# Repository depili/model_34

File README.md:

# Files for Model 34 tape and card punch control

The circuit is based on the example in the manual. This repository includes the hardware as a kicad project, the software for the arduino for usb serial communications and a 3d printable drive belt replacement.

The belt was printed in TPU and seems to last well, at least in light use.

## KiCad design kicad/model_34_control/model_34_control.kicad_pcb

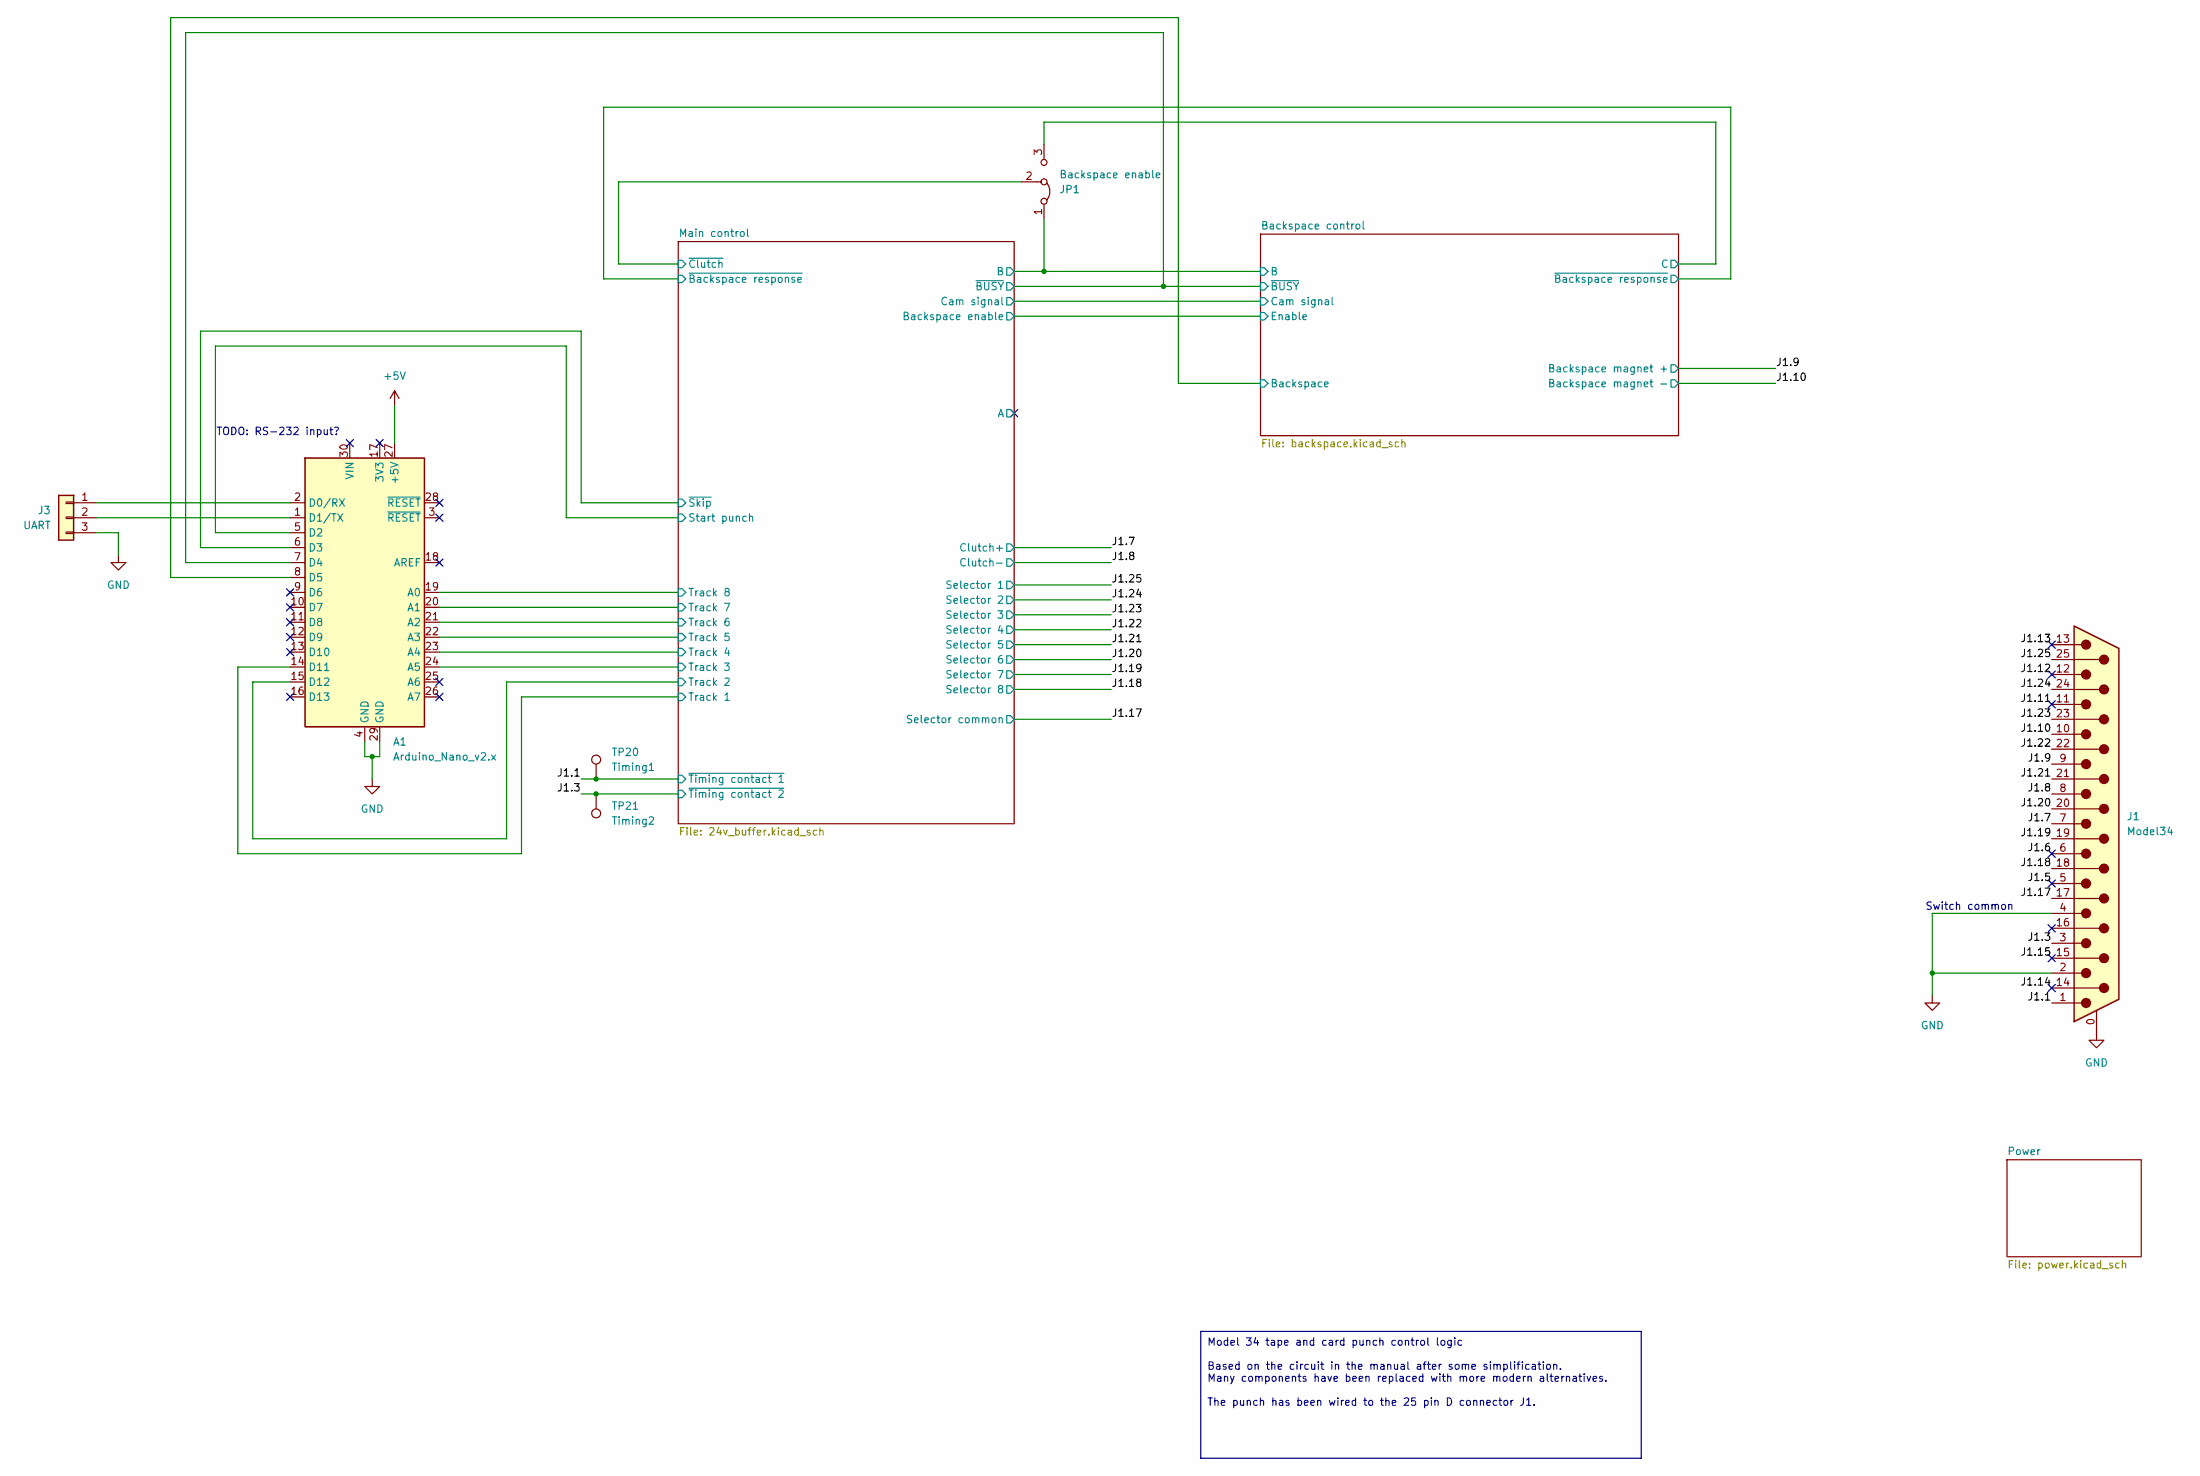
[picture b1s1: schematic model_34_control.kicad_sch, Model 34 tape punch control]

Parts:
A1: Arduino_Nano_v2.x; Arduino_Nano
J1: Model34; DSUB-25_Female_Horizontal_P2.77x2.84mm_EdgePinOffset9.90mm_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
J3: UART; PinHeader_1x03_P2.54mm_Vertical
JP1: Backspace enable; PinHeader_1x03_P2.54mm_Vertical
TP20: Timing1; TestPoint_Loop_D2.54mm_Drill1.5mm_Beaded
TP21: Timing2; TestPoint_Loop_D2.54mm_Drill1.5mm_Beaded

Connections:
+5V: A1.27 (+5V); also elsewhere on the board
+24V: J1.7, J1.9, J1.17; also elsewhere on the board
/Backspace control/B: JP1.1 (A); also elsewhere on the board
/Backspace control/Backspace: A1.8 (D5); also elsewhere on the board
/Backspace control/C: JP1.3 (B); also elsewhere on the board
/Backspace control/~BUSY: A1.7 (D4); also elsewhere on the board
/J1.1: J1.1, TP20.1; also elsewhere on the board
/J1.3: J1.3, TP21.1; also elsewhere on the board
/J1.5: J1.5
/J1.6: J1.6
/J1.8: J1.8; also elsewhere on the board
/J1.10: J1.10; also elsewhere on the board
/J1.11: J1.11
/J1.12: J1.12
/J1.13: J1.13
/J1.14: J1.14
/J1.15: J1.15
/J1.18: J1.18; also elsewhere on the board
/J1.19: J1.19; also elsewhere on the board
/J1.20: J1.20; also elsewhere on the board
/J1.21: J1.21; also elsewhere on the board
/J1.22: J1.22; also elsewhere on the board
/J1.23: J1.23; also elsewhere on the board
/J1.24: J1.24; also elsewhere on the board
/J1.25: J1.25; also elsewhere on the board
/Main control/Start punch: A1.5 (D2); also elsewhere on the board
/Main control/Track 1: A1.14 (D11); also elsewhere on the board
/Main control/Track 2: A1.15 (D12); also elsewhere on the board
/Main control/Track 3: A1.24 (A5); also elsewhere on the board
/Main control/Track 4: A1.23 (A4); also elsewhere on the board
/Main control/Track 5: A1.22 (A3); also elsewhere on the board
/Main control/Track 6: A1.21 (A2); also elsewhere on the board
/Main control/Track 7: A1.20 (A1); also elsewhere on the board
/Main control/Track 8: A1.19 (A0); also elsewhere on the board
/Main control/~Clutch: JP1.2 (C); also elsewhere on the board
/Main control/~Skip: A1.6 (D3); also elsewhere on the board
GND: A1.4 (GND), A1.29 (GND), J1.0 (PAD), J1.2, J1.4, J3.3; also elsewhere on the board
unnamed: A1.2 (D0/RX), J3.1
unnamed: A1.1 (D1/TX), J3.2

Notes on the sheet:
Model 34 tape and card punch control logic Based on the circuit in the manual after some simplification. Many components have been replaced with more modern alternatives. The punch has been wired to the 25 pin D connector J1.
TODO: RS-232 input?
Switch common

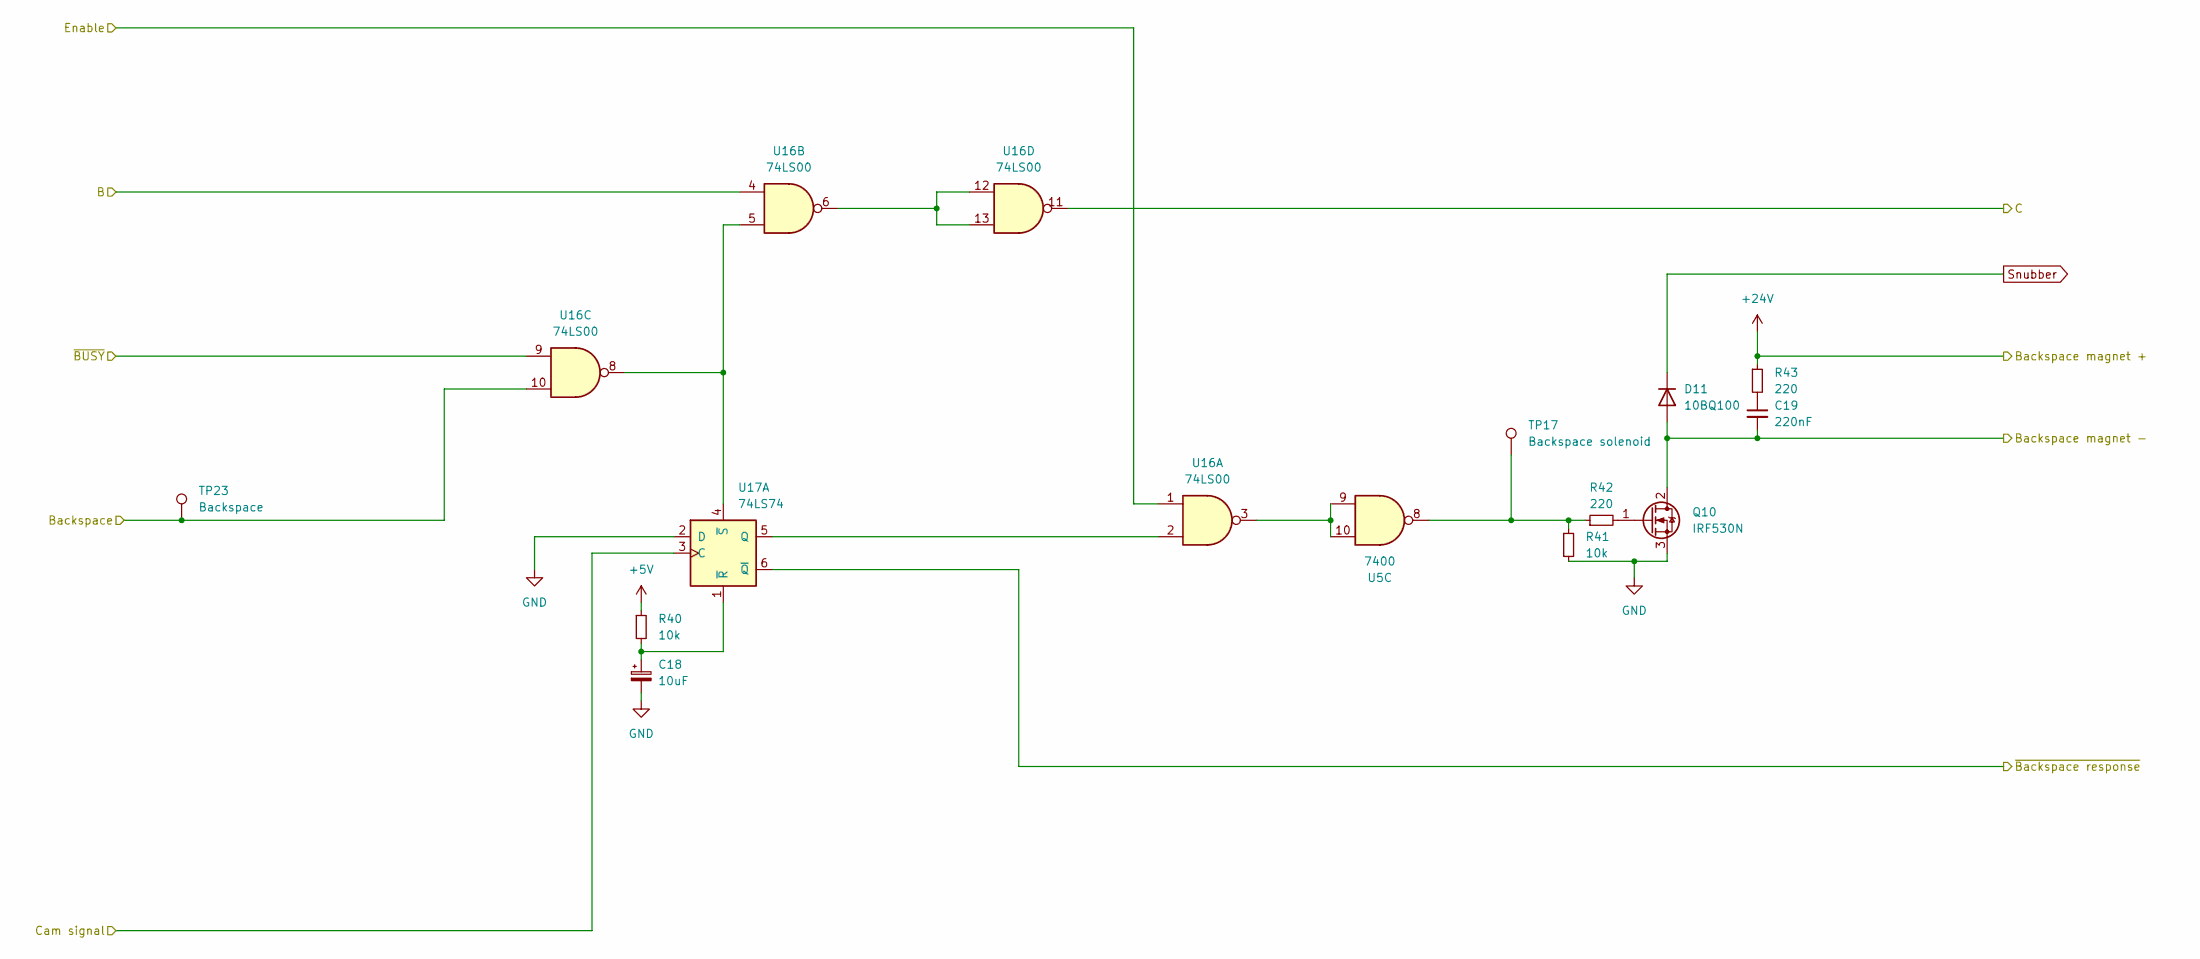
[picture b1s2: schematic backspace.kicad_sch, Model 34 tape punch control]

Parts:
C18: 10uF; CP_EIA-3528-21_Kemet-B_Pad1.50x2.35mm_HandSolder
C19: 220nF; C_0805_2012Metric_Pad1.18x1.45mm_HandSolder
D11: 10BQ100; D_SMA-SMB_Universal_Handsoldering
Q10: IRF530N; TO-220-3_Vertical
R40, R41: 10k; R_0805_2012Metric_Pad1.20x1.40mm_HandSolder
R42, R43: 220; R_0805_2012Metric_Pad1.20x1.40mm_HandSolder
TP17: Backspace solenoid; TestPoint_Loop_D2.54mm_Drill1.5mm_Beaded
TP23: Backspace; TestPoint_Loop_D2.54mm_Drill1.5mm_Beaded
U5: 7400; SOIC-14_3.9x8.7mm_P1.27mm
U16: 74LS00; SOIC-14_3.9x8.7mm_P1.27mm
U17: 74LS74; SOIC-14_3.9x8.7mm_P1.27mm

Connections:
+5V: R40.1; also elsewhere on the board
+24V: R43.1; also elsewhere on the board
/Backspace control/B: U16.4; also elsewhere on the board
/Backspace control/Backspace: TP23.1, U16.10; also elsewhere on the board
/Backspace control/C: U16.11; also elsewhere on the board
/Backspace control/Cam signal: U17.3 (C); also elsewhere on the board
/Backspace control/Enable: U16.1; also elsewhere on the board
/Backspace control/~BUSY: U16.9; also elsewhere on the board
/Backspace control/~Backspace response: U17.6 (~Q); also elsewhere on the board
/J1.10: C19.2, D11.2 (A), Q10.2 (D); also elsewhere on the board
GND: C18.2, Q10.3 (S), R41.2, U17.2 (D); also elsewhere on the board
unnamed: C19.1, R43.2
unnamed: Q10.1 (G), R42.2
unnamed: R41.1, R42.1, TP17.1, U5.8
unnamed: U5.9, U5.10, U16.3
unnamed: U16.6, U16.12, U16.13
unnamed: U16.2, U17.5 (Q)
unnamed: C18.1, R40.2, U17.1 (~R)
unnamed: U16.5, U16.8, U17.4 (~S)
Snubber: D11.1 (K); also elsewhere on the board

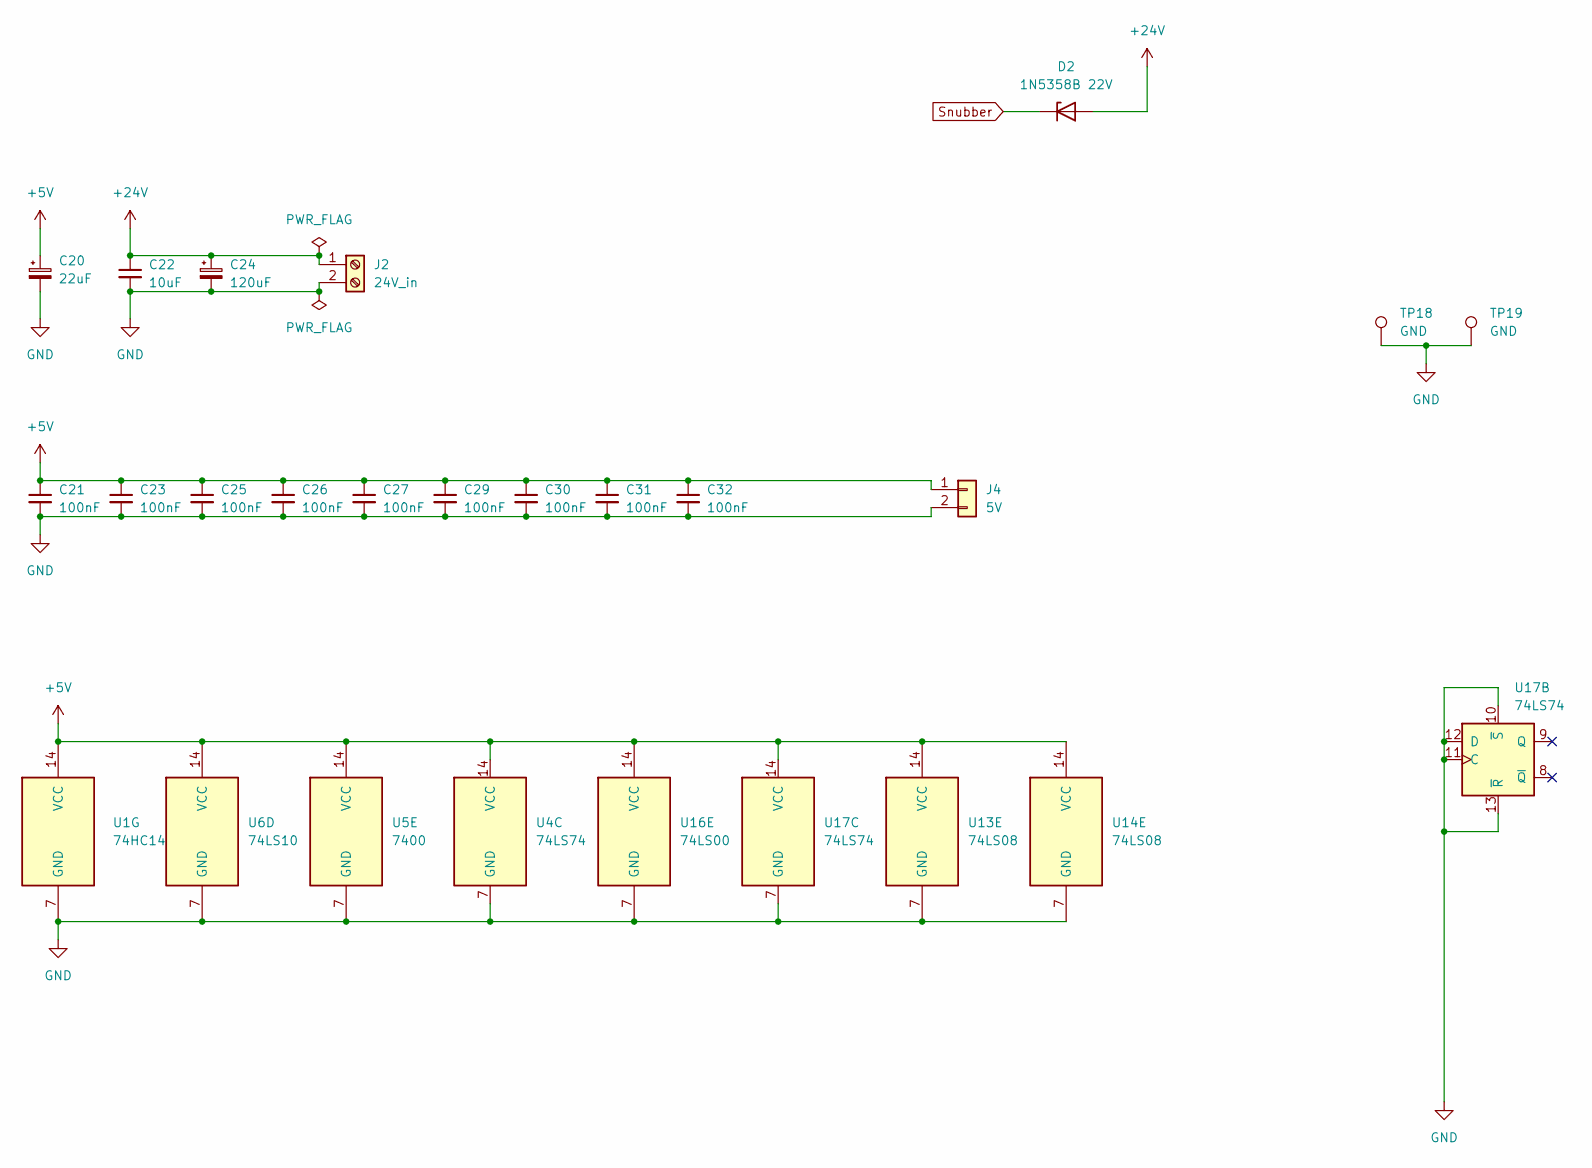
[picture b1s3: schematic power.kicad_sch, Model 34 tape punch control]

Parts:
C20: 22uF; CP_EIA-3528-21_Kemet-B_Pad1.50x2.35mm_HandSolder
C21, C23, C25, C26, C27, C29, C30, C31, C32: 100nF; C_0805_2012Metric_Pad1.18x1.45mm_HandSolder
C22: 10uF; C_1206_3216Metric_Pad1.33x1.80mm_HandSolder
C24: 120uF; CP_Elec_10x10.5
D2: 1N5358B 22V; D_DO-201AE_P15.24mm_Horizontal
J2: 24V_in; TerminalBlock_MetzConnect_Type073_RT02602HBLU_1x02_P5.08mm_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
J4: 5V; PinHeader_1x02_P2.54mm_Vertical
TP18, TP19: GND; TestPoint_Loop_D2.54mm_Drill1.5mm_Beaded
U1: 74HC14; SOIC-14_3.9x8.7mm_P1.27mm
U4, U17: 74LS74; SOIC-14_3.9x8.7mm_P1.27mm
U5: 7400; SOIC-14_3.9x8.7mm_P1.27mm
U6: 74LS10; SOIC-14_3.9x8.7mm_P1.27mm
U13, U14: 74LS08; SOIC-14_3.9x8.7mm_P1.27mm
U16: 74LS00; SOIC-14_3.9x8.7mm_P1.27mm

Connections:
+5V: C20.1, C21.1, C23.1, C25.1, C26.1, C27.1, C29.1, C30.1, C31.1, C32.1, J4.1, U1.14 (VCC), U4.14 (VCC), U5.14 (VCC), U6.14 (VCC), U13.14 (VCC), U14.14 (VCC), U16.14 (VCC), U17.14 (VCC); also elsewhere on the board
+24V: C22.1, C24.1, D2.2 (A), J2.1; also elsewhere on the board
GND: C20.2, C21.2, C22.2, C23.2, C24.2, C25.2, C26.2, C27.2, C29.2, C30.2, C31.2, C32.2, J2.2, J4.2, TP18.1, TP19.1, U1.7 (GND), U4.7 (GND), U5.7 (GND), U6.7 (GND), U13.7 (GND), U14.7 (GND), U16.7 (GND), U17.7 (GND), U17.10 (~S), U17.11 (C), U17.12 (D), U17.13 (~R); also elsewhere on the board
Snubber: D2.1 (K); also elsewhere on the board

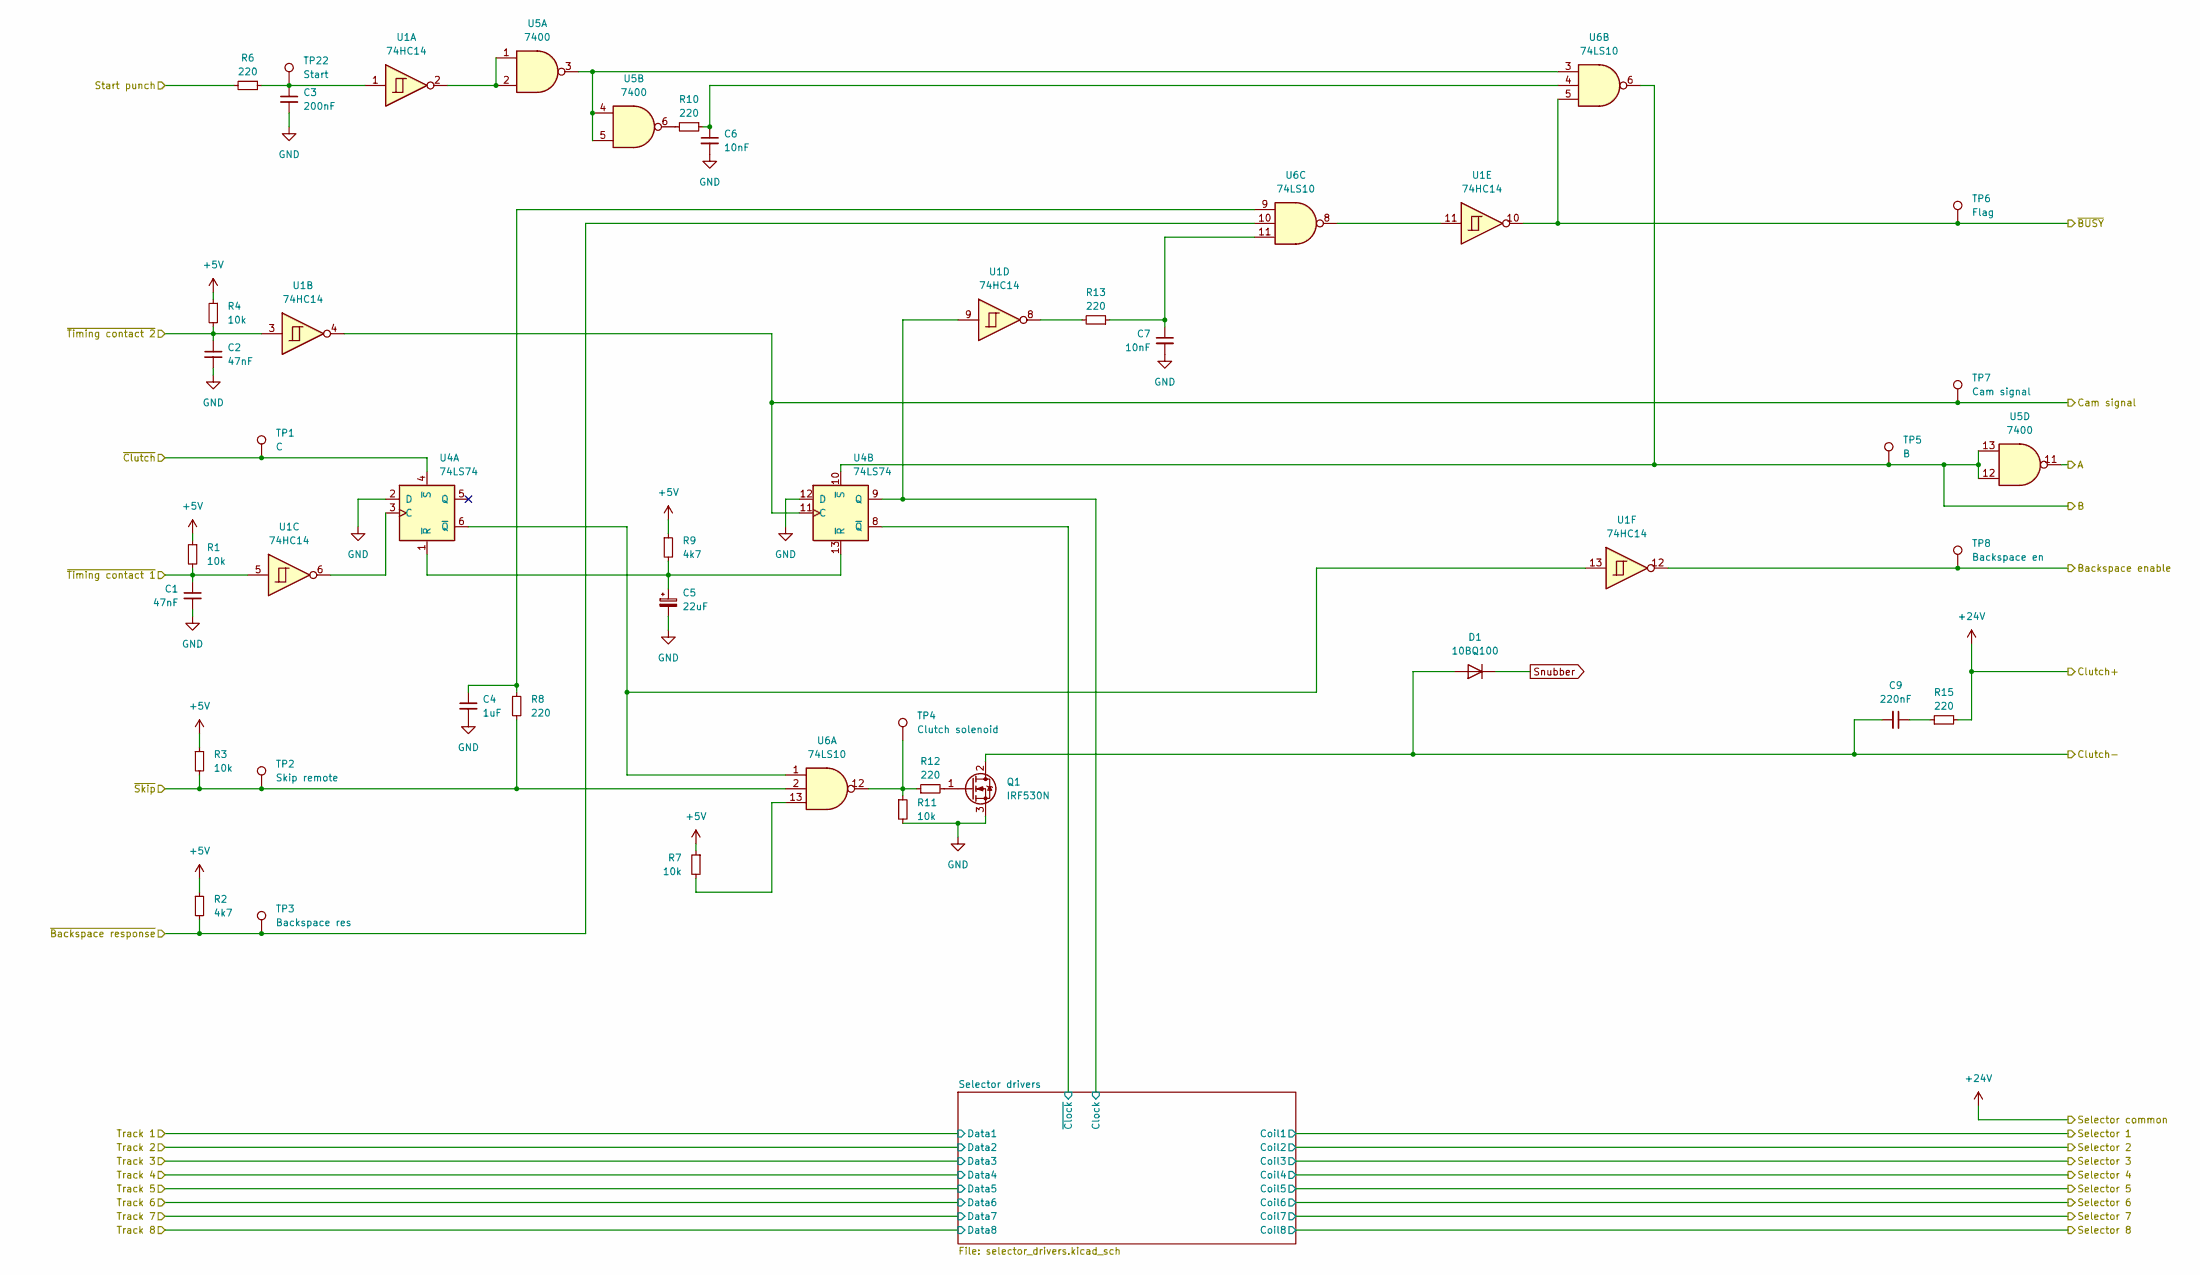
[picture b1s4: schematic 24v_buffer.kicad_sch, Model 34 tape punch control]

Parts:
C1, C2: 47nF; C_0805_2012Metric_Pad1.18x1.45mm_HandSolder
C3: 200nF; C_0805_2012Metric_Pad1.18x1.45mm_HandSolder
C4: 1uF; C_0805_2012Metric_Pad1.18x1.45mm_HandSolder
C5: 22uF; CP_EIA-3528-21_Kemet-B_Pad1.50x2.35mm_HandSolder
C6, C7: 10nF; C_0805_2012Metric_Pad1.18x1.45mm_HandSolder
C9: 220nF; C_0805_2012Metric_Pad1.18x1.45mm_HandSolder
D1: 10BQ100; D_SMA-SMB_Universal_Handsoldering
Q1: IRF530N; TO-220-3_Vertical
R1, R3, R4, R7, R11: 10k; R_0805_2012Metric_Pad1.20x1.40mm_HandSolder
R2, R9: 4k7; R_0805_2012Metric_Pad1.20x1.40mm_HandSolder
R6, R8, R10, R12, R13, R15: 220; R_0805_2012Metric_Pad1.20x1.40mm_HandSolder
TP1: C; TestPoint_Loop_D2.54mm_Drill1.5mm_Beaded
TP2: Skip remote; TestPoint_Loop_D2.54mm_Drill1.5mm_Beaded
TP3: Backspace res; TestPoint_Loop_D2.54mm_Drill1.5mm_Beaded
TP4: Clutch solenoid; TestPoint_Loop_D2.54mm_Drill1.5mm_Beaded
TP5: B; TestPoint_Loop_D2.54mm_Drill1.5mm_Beaded
TP6: Flag; TestPoint_Loop_D2.54mm_Drill1.5mm_Beaded
TP7: Cam signal; TestPoint_Loop_D2.54mm_Drill1.5mm_Beaded
TP8: Backspace en; TestPoint_Loop_D2.54mm_Drill1.5mm_Beaded
TP22: Start; TestPoint_Loop_D2.54mm_Drill1.5mm_Beaded
U1: 74HC14; SOIC-14_3.9x8.7mm_P1.27mm
U4: 74LS74; SOIC-14_3.9x8.7mm_P1.27mm
U5: 7400; SOIC-14_3.9x8.7mm_P1.27mm
U6: 74LS10; SOIC-14_3.9x8.7mm_P1.27mm

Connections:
+5V: R1.1, R2.1, R3.1, R4.1, R7.1, R9.1; also elsewhere on the board
+24V: R15.2; also elsewhere on the board
/Backspace control/B: TP5.1, U4.10 (~S), U5.12, U5.13, U6.6; also elsewhere on the board
/Backspace control/Cam signal: TP7.1, U1.4, U4.11 (C); also elsewhere on the board
/Backspace control/Enable: TP8.1, U1.12; also elsewhere on the board
/Backspace control/~BUSY: TP6.1, U1.10, U6.5; also elsewhere on the board
/Backspace control/~Backspace response: R2.2, TP3.1, U6.10; also elsewhere on the board
/J1.1: C1.1, R1.2, U1.5; also elsewhere on the board
/J1.3: C2.1, R4.2, U1.3; also elsewhere on the board
/J1.8: C9.2, D1.2 (A), Q1.2 (D); also elsewhere on the board
/Main control/A: U5.11
/Main control/Selector drivers/Clock: U1.9, U4.9 (Q); also elsewhere on the board
/Main control/Selector drivers/~Clock: U4.8 (~Q); also elsewhere on the board
/Main control/Start punch: R6.2; also elsewhere on the board
/Main control/~Clutch: TP1.1, U4.4 (~S); also elsewhere on the board
/Main control/~Skip: R3.2, R8.2, TP2.1, U6.2; also elsewhere on the board
GND: C1.2, C2.2, C3.2, C4.2, C5.2, C6.2, C7.2, Q1.3 (S), R11.2, U4.2 (D), U4.12 (D); also elsewhere on the board
unnamed: C3.1, R6.1, TP22.1, U1.1
unnamed: C4.1, R8.1, U6.9
unnamed: C6.1, R10.1, U6.4
unnamed: C7.1, R13.1, U6.11
unnamed: C9.1, R15.1
unnamed: Q1.1 (G), R12.2
unnamed: R7.2, U6.13
unnamed: R10.2, U5.6
unnamed: R11.1, R12.1, TP4.1, U6.12
unnamed: R13.2, U1.8
unnamed: U1.2, U5.1, U5.2
unnamed: U1.11, U6.8
unnamed: U1.6, U4.3 (C)
unnamed: U1.13, U4.6 (~Q), U6.1
unnamed: C5.1, R9.2, U4.1 (~R), U4.13 (~R)
unnamed: U5.3, U5.4, U5.5, U6.3
Snubber: D1.1 (K); also elsewhere on the board

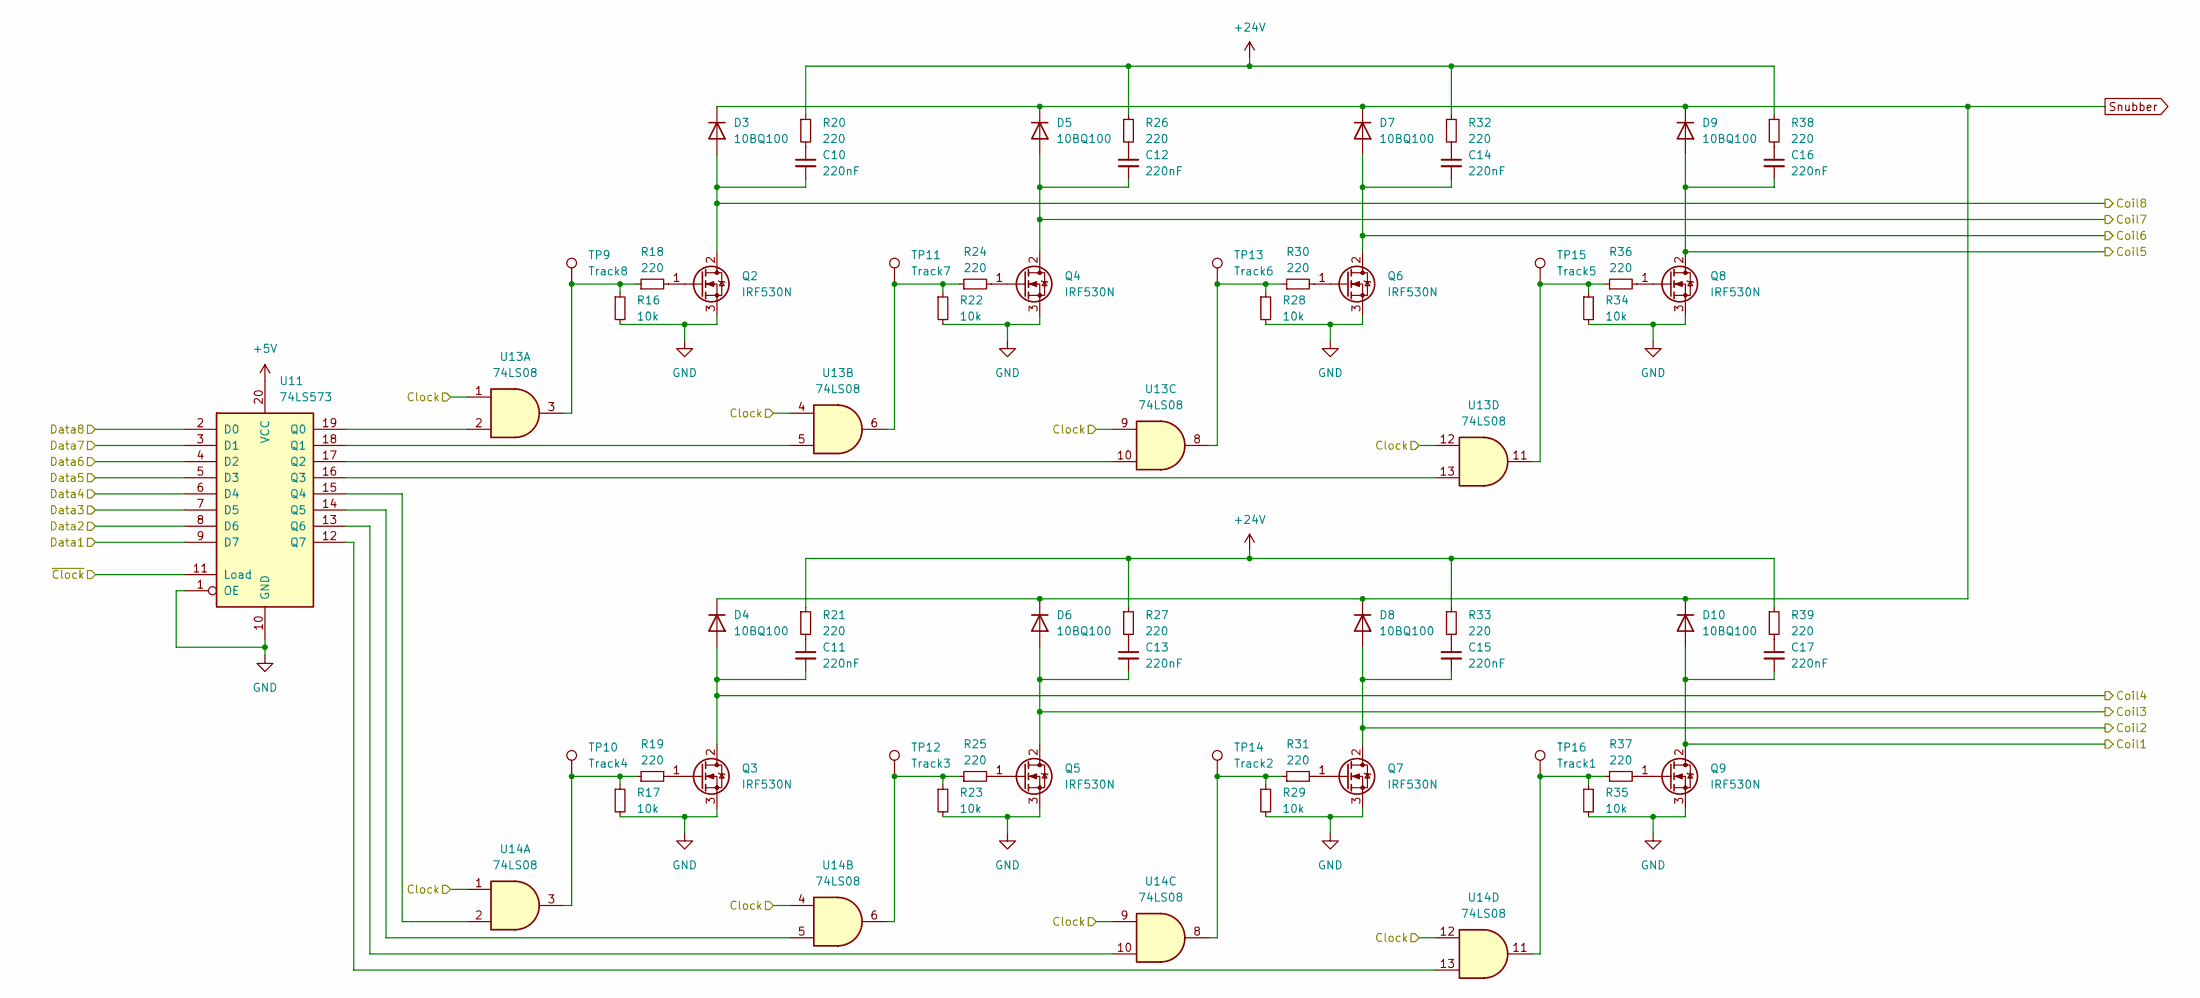
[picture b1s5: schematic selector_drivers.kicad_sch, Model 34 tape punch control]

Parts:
C10, C11, C12, C13, C14, C15, C16, C17: 220nF; C_0805_2012Metric_Pad1.18x1.45mm_HandSolder
D3, D4, D5, D6, D7, D8, D9, D10: 10BQ100; D_SMA-SMB_Universal_Handsoldering
Q2, Q3, Q4, Q5, Q6, Q7, Q8, Q9: IRF530N; TO-220-3_Vertical
R16, R17, R22, R23, R28, R29, R34, R35: 10k; R_0805_2012Metric_Pad1.20x1.40mm_HandSolder
R18, R19, R20, R21, R24, R25, R26, R27, R30, R31, R32, R33, R36, R37, R38, R39: 220; R_0805_2012Metric_Pad1.20x1.40mm_HandSolder
TP9: Track8; TestPoint_Loop_D2.54mm_Drill1.5mm_Beaded
TP10: Track4; TestPoint_Loop_D2.54mm_Drill1.5mm_Beaded
TP11: Track7; TestPoint_Loop_D2.54mm_Drill1.5mm_Beaded
TP12: Track3; TestPoint_Loop_D2.54mm_Drill1.5mm_Beaded
TP13: Track6; TestPoint_Loop_D2.54mm_Drill1.5mm_Beaded
TP14: Track2; TestPoint_Loop_D2.54mm_Drill1.5mm_Beaded
TP15: Track5; TestPoint_Loop_D2.54mm_Drill1.5mm_Beaded
TP16: Track1; TestPoint_Loop_D2.54mm_Drill1.5mm_Beaded
U11: 74LS573; SOIC-20W_7.5x12.8mm_P1.27mm
U13, U14: 74LS08; SOIC-14_3.9x8.7mm_P1.27mm

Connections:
+5V: U11.20 (VCC); also elsewhere on the board
+24V: R20.1, R21.1, R26.1, R27.1, R32.1, R33.1, R38.1, R39.1; also elsewhere on the board
/J1.18: C10.2, D3.2 (A), Q2.2 (D); also elsewhere on the board
/J1.19: C12.2, D5.2 (A), Q4.2 (D); also elsewhere on the board
/J1.20: C14.2, D7.2 (A), Q6.2 (D); also elsewhere on the board
/J1.21: C16.2, D9.2 (A), Q8.2 (D); also elsewhere on the board
/J1.22: C11.2, D4.2 (A), Q3.2 (D); also elsewhere on the board
/J1.23: C13.2, D6.2 (A), Q5.2 (D); also elsewhere on the board
/J1.24: C15.2, D8.2 (A), Q7.2 (D); also elsewhere on the board
/J1.25: C17.2, D10.2 (A), Q9.2 (D); also elsewhere on the board
/Main control/Selector drivers/Clock: U13.1, U13.4, U13.9, U13.12, U14.1, U14.4, U14.9, U14.12; also elsewhere on the board
/Main control/Selector drivers/~Clock: U11.11 (Load); also elsewhere on the board
/Main control/Track 1: U11.9 (D7); also elsewhere on the board
/Main control/Track 2: U11.8 (D6); also elsewhere on the board
/Main control/Track 3: U11.7 (D5); also elsewhere on the board
/Main control/Track 4: U11.6 (D4); also elsewhere on the board
/Main control/Track 5: U11.5 (D3); also elsewhere on the board
/Main control/Track 6: U11.4 (D2); also elsewhere on the board
/Main control/Track 7: U11.3 (D1); also elsewhere on the board
/Main control/Track 8: U11.2 (D0); also elsewhere on the board
GND: Q2.3 (S), Q3.3 (S), Q4.3 (S), Q5.3 (S), Q6.3 (S), Q7.3 (S), Q8.3 (S), Q9.3 (S), R16.2, R17.2, R22.2, R23.2, R28.2, R29.2, R34.2, R35.2, U11.1 (OE), U11.10 (GND); also elsewhere on the board
unnamed: C10.1, R20.2
unnamed: C11.1, R21.2
unnamed: C12.1, R26.2
unnamed: C13.1, R27.2
unnamed: C14.1, R32.2
unnamed: C15.1, R33.2
unnamed: C16.1, R38.2
unnamed: C17.1, R39.2
unnamed: Q2.1 (G), R18.2
unnamed: Q3.1 (G), R19.2
unnamed: Q4.1 (G), R24.2
unnamed: Q5.1 (G), R25.2
unnamed: Q6.1 (G), R30.2
unnamed: Q7.1 (G), R31.2
unnamed: Q8.1 (G), R36.2
unnamed: Q9.1 (G), R37.2
unnamed: R16.1, R18.1, TP9.1, U13.3
unnamed: R17.1, R19.1, TP10.1, U14.3
unnamed: R22.1, R24.1, TP11.1, U13.6
unnamed: R23.1, R25.1, TP12.1, U14.6
unnamed: R28.1, R30.1, TP13.1, U13.8
unnamed: R29.1, R31.1, TP14.1, U14.8
unnamed: R34.1, R36.1, TP15.1, U13.11
unnamed: R35.1, R37.1, TP16.1, U14.11
unnamed: U11.19 (Q0), U13.2
unnamed: U11.18 (Q1), U13.5
unnamed: U11.17 (Q2), U13.10
unnamed: U11.16 (Q3), U13.13
unnamed: U11.15 (Q4), U14.2
unnamed: U11.14 (Q5), U14.5
unnamed: U11.13 (Q6), U14.10
unnamed: U11.12 (Q7), U14.13
Snubber: D3.1 (K), D4.1 (K), D5.1 (K), D6.1 (K), D7.1 (K), D8.1 (K), D9.1 (K), D10.1 (K); also elsewhere on the board

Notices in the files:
kicad/model_34_control/24v_buffer.kicad_sch:
License: CERN-OHL-P
